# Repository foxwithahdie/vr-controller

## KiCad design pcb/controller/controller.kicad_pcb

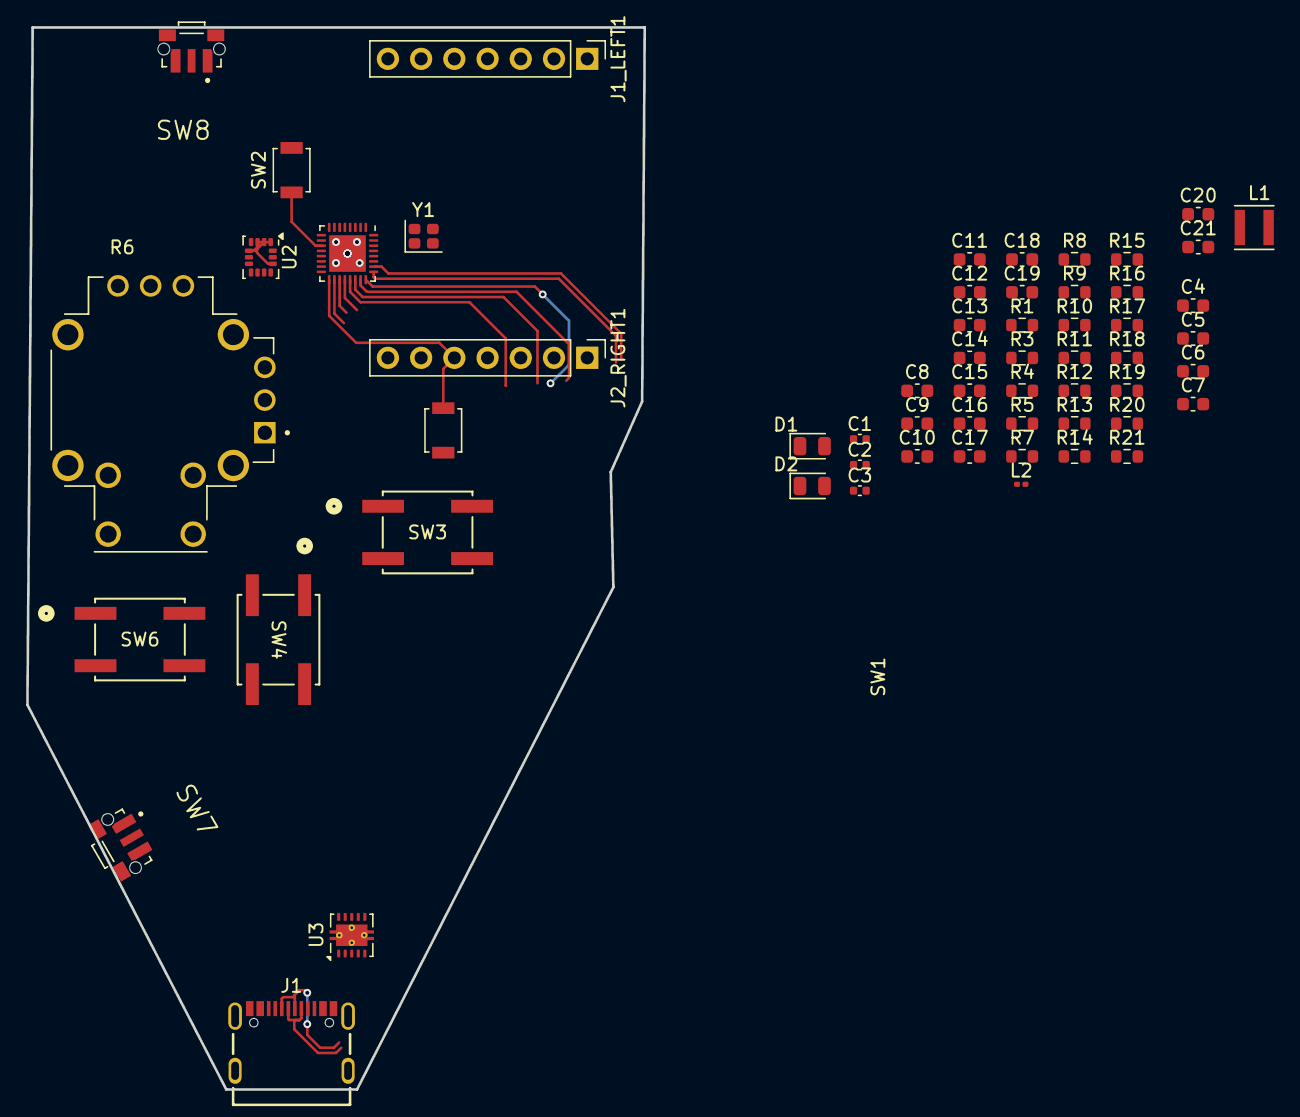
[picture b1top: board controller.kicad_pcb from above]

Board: 2 copper layers, 47.2 x 81.2 mm, 59 parts (0 on the bottom side), 37 nets.

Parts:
C1, C2: 13pF; C_0402_1005Metric
C3: 10nF; C_0402_1005Metric
C4, C7, C10, C11, C20, C21: 0.1uF; C_0603_1608Metric
C5, C6: 1uF; C_0603_1608Metric
C8, C9, C12, C13, C14, C15: 10uF; C_0603_1608Metric
C16, C17: 100nF; C_0603_1608Metric
C18, C19: C; C_0603_1608Metric
D1, D2: LED; LED_0805_2012Metric
J1: USB4105-GF-A
J1_LEFT1, J2_RIGHT1: Conn_01x07; PinHeader_1x07_P2.54mm_Vertical
L1: 2.2uH; IND_LQH3NPZ2R2MMEL
L2: 24nH; L_0201_0603Metric
R1, R17, R18, R21: 1K; R_0603_1608Metric
R3, R4, R10, R11, R12, R13, R14, R15, R16: 10K; R_0603_1608Metric
R5: 0; R_0603_1608Metric
R6: THB001P; CNK_THB001P
R7, R8: 27; R_0603_1608Metric
R9: 100; R_0603_1608Metric
R19, R20: 5.1K; R_0603_1608Metric
SW1, SW2: SW_Push; SW_SPST_B3U-1000P
SW3, SW4, SW6: EVQ-Q2K03W; EVQ-Q2K03W_PAN
SW7, SW8: TL3340AF160QG; SW_TL3340AF160QG
U1: ESP32-H2; QFN-32-1EP_4x4mm_P0.4mm_EP2.9x2.9mm
U2: LSM6DSM; LGA-14_3x2.5mm_P0.5mm_LayoutBorder3x4y
U3: TPS63001; Texas_DRC0010J_ThermalVias
Y1: ECS-320-10-37B-CKY-TR; Crystal_SMD_2016-4Pin_2.0x1.6mm

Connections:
+3V3: C3.2, C4.2, C9.1, C10.2, C11.2, C12.2, C13.2, C14.2, C15.1, C16.2, C17.1, J2_RIGHT1.4, R1.1, R3.1, R4.1, R5.1, R10.2, R11.2, R12.1, R13.1, R14.1, R15.1, R16.1, R17.2, R21.1, U1.1 (VDD3P3), U1.2 (VDD3P3), U1.9 (VDDPST1), U1.19 (VDDA_PMU), U1.20 (VDDPST2), U1.27 (VDD3P3), U1.30 (VDD3P3), U1.31 (VDD3P3), U2.1 (SDO/SA0), U2.2 (SDX), U2.3 (SCX), U2.5 (VDDIO), U2.8 (VDD), U2.12 (CS), U3.1 (VOUT), U3.10 (FB)
/BOOT: C5.1, R3.2, SW2.1, U1.11 (GPIO9)
/BUTTON_PRESS_1: R13.2, SW3.1, SW3.2, U1.24 (GPIO25/FSPICS3)
/BUTTON_PRESS_2: R14.2, SW4.1, SW4.2, U1.22 (U0RXD/GPIO23/FSPICS1)
/BUTTON_PRESS_3: R15.2, R16.2, SW6.1, SW6.2, U1.23 (U0TXD/GPIO24/FSPICS2)
/BUTTON_TRIGGER_1: SW7.1, U1.15 (GPIO13/XTAL_32K_P)
/BUTTON_TRIGGER_2: SW8.1, U1.16 (GPIO14/XTAL_32K_N)
/D+: C18.1, R8.1, U1.26 (USB_D+/GPIO27/FSPICS5)
/D-: C19.2, R7.1, U1.25 (USB_D-/GPIO26/FSPICS4)
/EN: C6.1, J2_RIGHT1.5, R4.2, SW1.2, U1.17 (CHIP_EN)
/IMU_I2C_SCL: R21.2, U1.13 (GPIO11/ZCD1), U2.13 (SCL)
/IMU_I2C_SDA: R1.2, U1.12 (GPIO10/ZCD0), U2.14 (SDA)
/JOYSTICK_SWITCH: R6.A, R6.B, R10.1, U1.14 (GPIO12)
/JOYSTICK_X: C20.1, U1.5 (MTMS/GPIO2/FSPIWP/ADC1_CH1)
/JOYSTICK_Y: C21.1, U1.6 (MTDO/GPIO3/FSPIHD/ADC1_CH2)
/USR_LED: R18.2, U1.21 (GPIO22)
/WIFI_CS: J1_LEFT1.2, U1.4 (GPIO1/FSPICS0/ADC1_CH0)
/WIFI_MISO: J1_LEFT1.1, U1.3 (GPIO0/FSPIQ)
/WIFI_MOSI: J1_LEFT1.5, U1.8 (MTDI/GPIO5/FSPID/ADC1_CH4)
/WIFI_SCLK: J1_LEFT1.4, U1.7 (MTCK/GPIO4/FSPICLK/ADC1_CH3)
/XTAL_N: C1.2, U1.28 (XTAL_N), Y1.3
/XTAL_P: L2.1, U1.29 (XTAL_P)
GND: C1.1, C2.1, C3.1, C4.1, C5.2, C6.2, C7.2, C8.2, C9.2, C10.1, C11.1, C12.1, C13.1, C14.1, C15.2, C16.1, C17.2, C18.2, C19.1, C20.2, C21.2, D1.1 (K), D2.1 (K), J1.A1B12 (GND), J1.B1A12 (GND), J1.S1 (SHELL), J1.S2 (SHELL), J1.S3 (SHELL), J1.S4 (SHELL), J2_RIGHT1.3, R6.C, R6.D, R19.2, R20.2, SW1.1, SW2.2, SW3.3, SW3.4, SW4.3, SW4.4, SW6.3, SW6.4, SW7.2, SW8.2, U1.33 (GND), U2.6 (GND), U2.7 (GND), U3.3 (PGND), U3.9 (GND), U3.11 (PGND), Y1.2 (G), Y1.4 (G)
unnamed: C2.2, L2.2, Y1.1
unnamed: D1.2 (A), R18.1
unnamed: D2.2 (A), R17.1
unnamed: J1.A5 (CC1), R19.1
unnamed: J1.B5 (CC2), R20.1
unnamed: J1.A6 (D+), J1.B6 (D+), R8.2
unnamed: J1.A7 (D-), J1.B7 (D-), R7.2
unnamed: R11.1, SW7.3
unnamed: R12.2, SW8.3
unnamed: R5.2, U1.18 (VBAT)
unnamed: C7.1, R9.1, U3.6 (EN), U3.7 (PS/SYNC), U3.8 (VINA)
unnamed: L1.1, U3.4 (L1)
unnamed: L1.2, U3.2 (L2)
VCC: C8.1, J1.A4B9 (VBUS), J1.B4A9 (VBUS), R9.2, U3.5 (VIN)

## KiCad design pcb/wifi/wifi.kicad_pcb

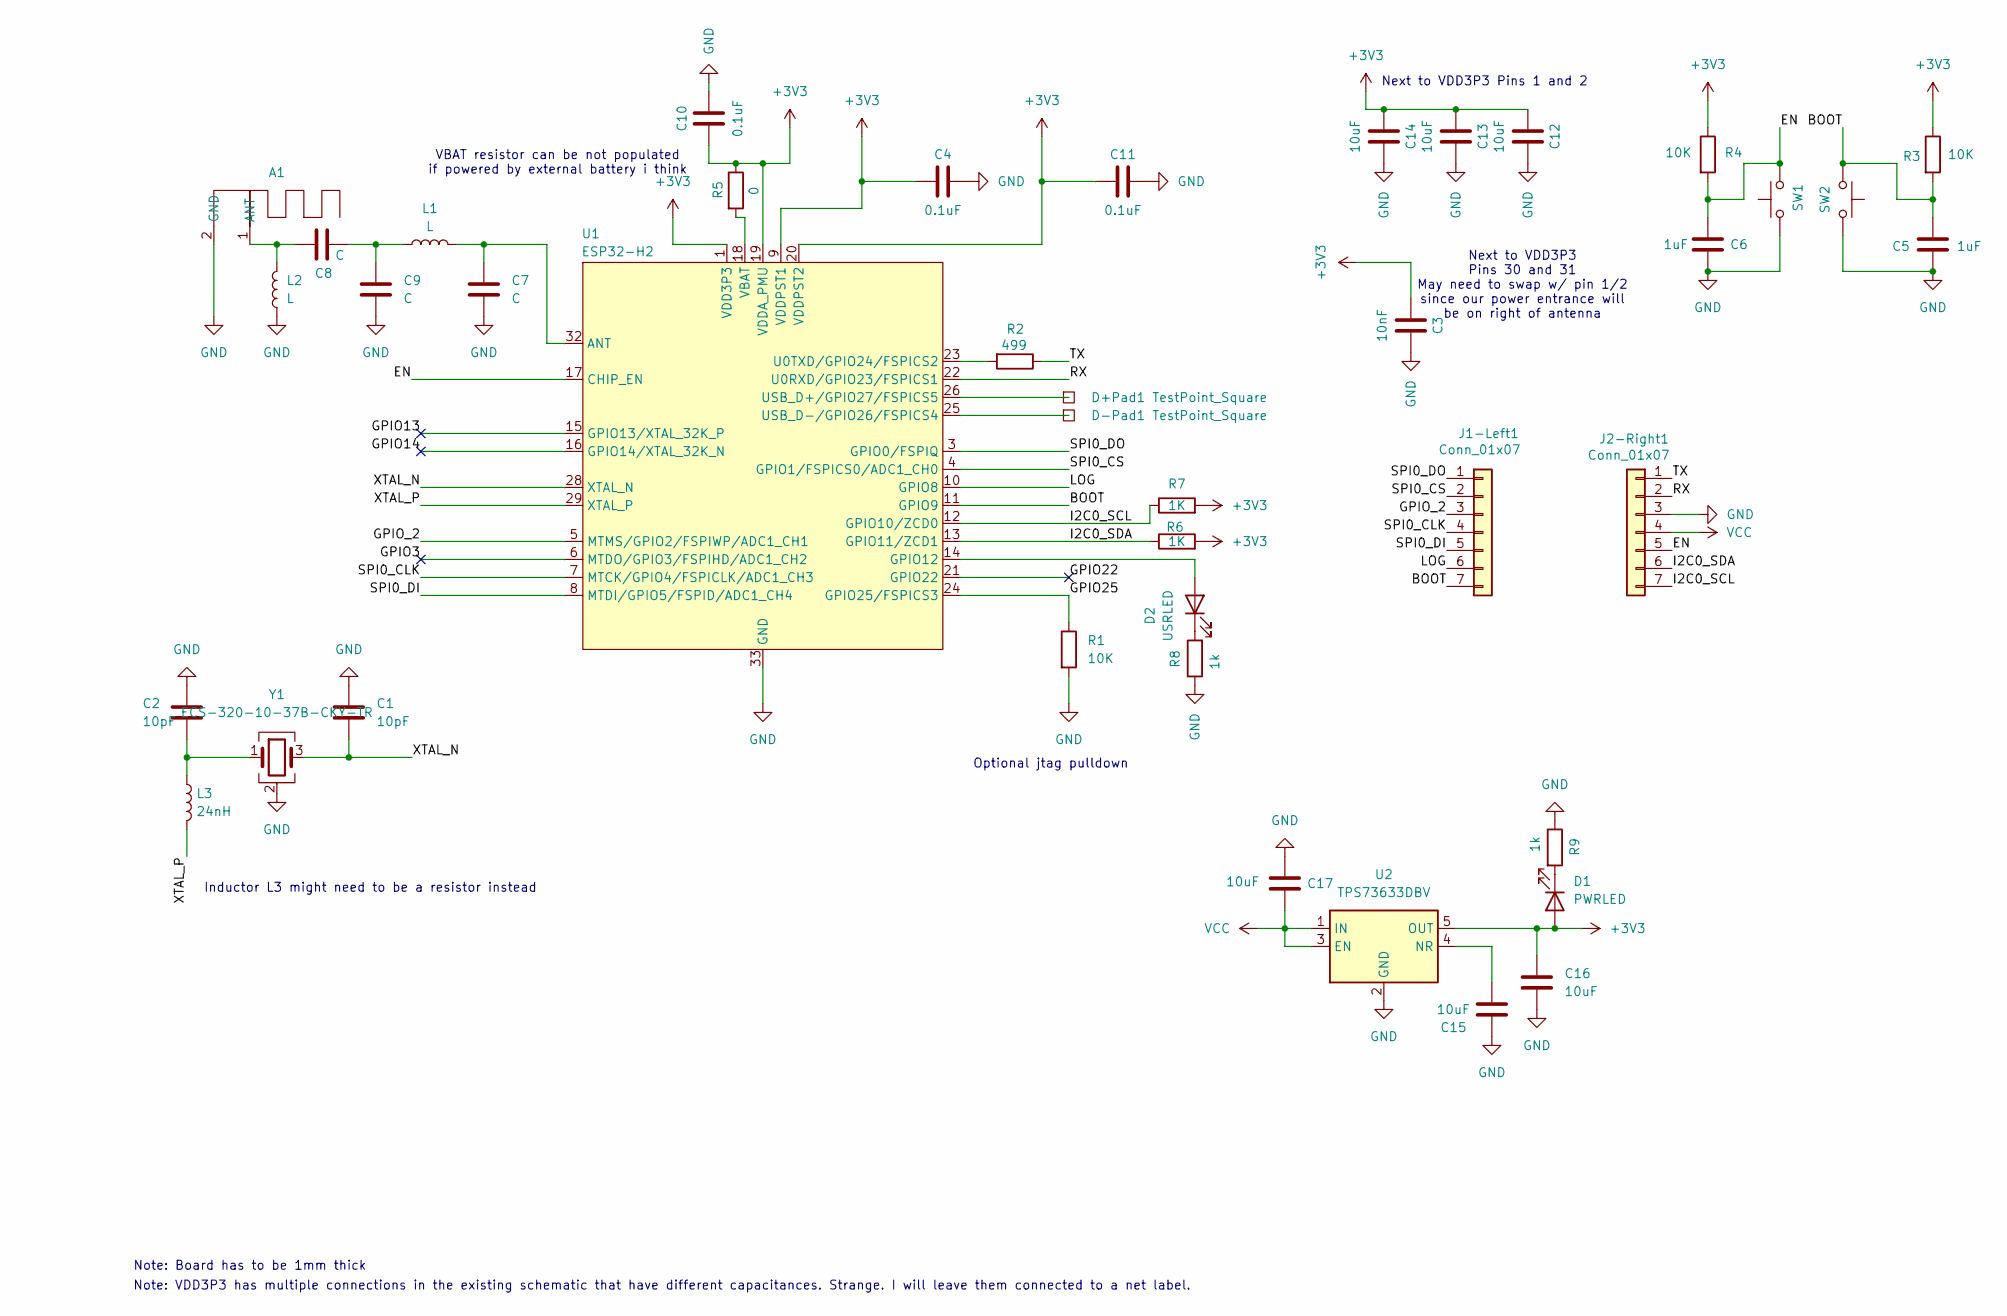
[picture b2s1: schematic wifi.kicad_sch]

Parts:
A1: ANT_MIFA_TI_AN043
C1, C2: 10pF; C_0402_1005Metric
C3: 10nF; C_0402_1005Metric
C4, C10, C11: 0.1uF; C_0402_1005Metric
C5, C6: 1uF; C_0603_1608Metric
C7, C8, C9: C; C_0201_0603Metric
C12, C13, C14, C15, C16, C17: 10uF; C_0603_1608Metric
D1: PWRLED; LED_0805_2012Metric_Pad1.15x1.40mm_HandSolder
D2: USRLED; LED_0805_2012Metric_Pad1.15x1.40mm_HandSolder
D+Pad1: TestPoint_Square; TestPoint_Pad_1.5x1.5mm
D-Pad1: TestPoint_Square; TestPoint_Pad_1.5x1.5mm
J1-Left1, J2-Right1: Conn_01x07; PinHeader_1x07_P2.54mm_Vertical
L1, L2: L; L_0201_0603Metric
L3: 24nH; L_0201_0603Metric
R1, R3, R4: 10K; R_0603_1608Metric
R2: 499; R_0402_1005Metric
R5: 0; R_0402_1005Metric
R6, R7: 1K; R_0603_1608Metric
R8, R9: 1k; R_0603_1608Metric
SW1, SW2: SW_Push; SW_SPST_B3U-1000P
U1: ESP32-H2; QFN-32-1EP_4x4mm_P0.4mm_EP2.9x2.9mm
U2: TPS73633DBV; SOT-23-5
Y1: ECS-320-10-37B-CKY-TR; Crystal_SMD_2016-4Pin_2.0x1.6mm

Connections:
+3V3: C3.2, C4.2, C10.2, C11.2, C12.2, C13.2, C14.2, C16.1, D1.2 (A), R3.1, R4.1, R5.1, R6.2, R7.2, U1.1 (VDD3P3), U1.2 (VDD3P3), U1.9 (VDDPST1), U1.19 (VDDA_PMU), U1.20 (VDDPST2), U1.27 (VDD3P3), U1.30 (VDD3P3), U1.31 (VDD3P3), U2.5 (OUT)
/BOOT: C5.1, J1-Left1.7, R3.2, SW2.1, U1.11 (GPIO9)
/EN: C6.1, J2-Right1.5, R4.2, SW1.2, U1.17 (CHIP_EN)
/GPIO3: U1.6 (MTDO/GPIO3/FSPIHD/ADC1_CH2)
/GPIO13: U1.15 (GPIO13/XTAL_32K_P)
/GPIO14: U1.16 (GPIO14/XTAL_32K_N)
/GPIO22: U1.21 (GPIO22)
/GPIO25: R1.1, U1.24 (GPIO25/FSPICS3)
/GPIO_2: J1-Left1.3, U1.5 (MTMS/GPIO2/FSPIWP/ADC1_CH1)
/I2C0_SCL: J2-Right1.7, R7.1, U1.12 (GPIO10/ZCD0)
/I2C0_SDA: J2-Right1.6, R6.1, U1.13 (GPIO11/ZCD1)
/LOG: J1-Left1.6, U1.10 (GPIO8)
/RX: J2-Right1.2, U1.22 (U0RXD/GPIO23/FSPICS1)
/SPI0_CLK: J1-Left1.4, U1.7 (MTCK/GPIO4/FSPICLK/ADC1_CH3)
/SPI0_CS: J1-Left1.2, U1.4 (GPIO1/FSPICS0/ADC1_CH0)
/SPI0_DI: J1-Left1.5, U1.8 (MTDI/GPIO5/FSPID/ADC1_CH4)
/SPI0_DO: J1-Left1.1, U1.3 (GPIO0/FSPIQ)
/TX: J2-Right1.1, R2.1
/XTAL_N: C1.2, U1.28 (XTAL_N), Y1.3
/XTAL_P: L3.2, U1.29 (XTAL_P)
GND: A1.2 (GND), C1.1, C2.1, C3.1, C4.1, C5.2, C6.2, C7.2, C9.2, C10.1, C11.1, C12.1, C13.1, C14.1, C15.2, C16.2, C17.1, J2-Right1.3, L2.1, R1.2, R8.1, R9.1, SW1.1, SW2.2, U1.33 (GND), U2.2 (GND), Y1.2 (G), Y1.4 (G)
unnamed: A1.1 (ANT), C8.1, L2.2
unnamed: C2.2, L3.1, Y1.1
unnamed: C8.2, C9.1, L1.1
unnamed: D1.1 (K), R9.2
unnamed: D2.2 (A), U1.14 (GPIO12)
unnamed: D2.1 (K), R8.2
unnamed: C7.1, L1.2, U1.32 (ANT)
unnamed: R2.2, U1.23 (U0TXD/GPIO24/FSPICS2)
unnamed: D+Pad1.1 (1_1), U1.26 (USB_D+/GPIO27/FSPICS5)
unnamed: D-Pad1.1 (1_1), U1.25 (USB_D-/GPIO26/FSPICS4)
unnamed: R5.2, U1.18 (VBAT)
unnamed: C15.1, U2.4 (NR)
VCC: C17.2, J2-Right1.4, U2.1 (IN), U2.3 (EN)

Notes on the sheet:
Inductor L3 might need to be a resistor instead
VBAT resistor can be not populated if powered by external battery i think
Optional jtag pulldown
Note: Board has to be 1mm thick
Note: VDD3P3 has multiple connections in the existing schematic that have different capacitances. Strange. I will leave them connected to a net label.
Next to VDD3P3 Pins 30 and 31 May need to swap w/ pin 1/2 since our power entrance will be on right of antenna
Next to VDD3P3 Pins 1 and 2

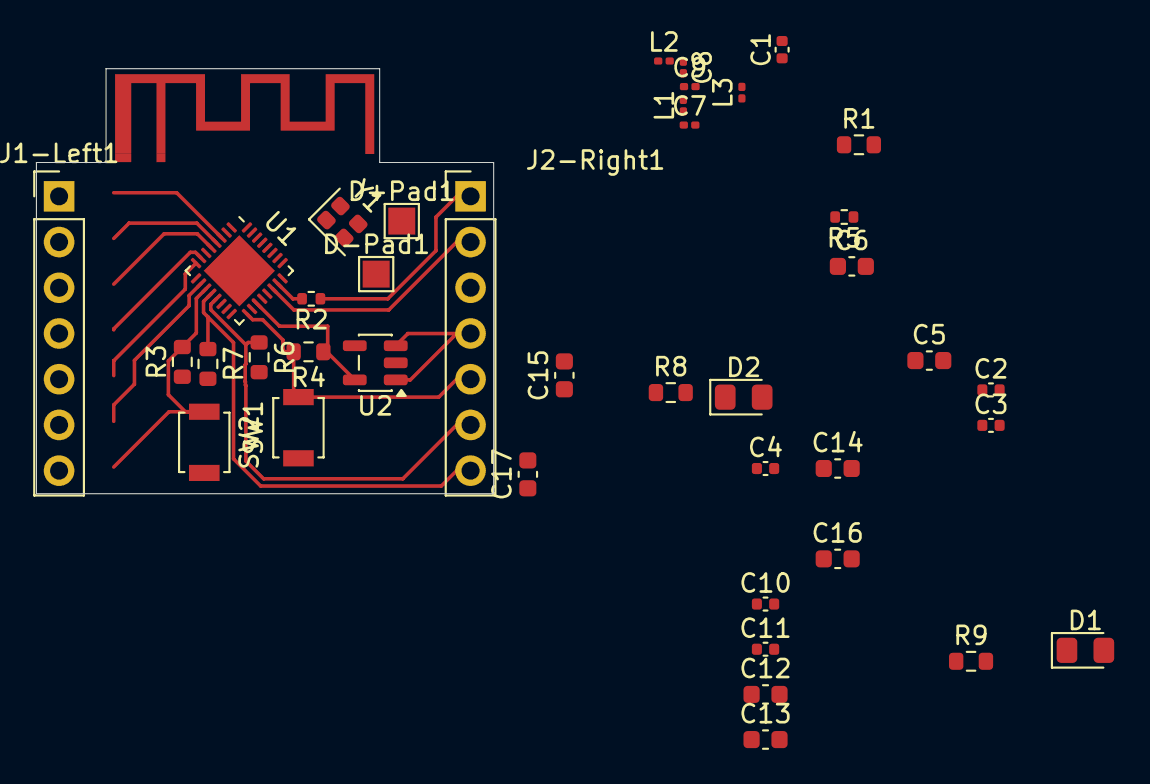
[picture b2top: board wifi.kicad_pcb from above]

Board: 2 copper layers, 25.4 x 23.6 mm, 41 parts (0 on the bottom side), 30 nets.
